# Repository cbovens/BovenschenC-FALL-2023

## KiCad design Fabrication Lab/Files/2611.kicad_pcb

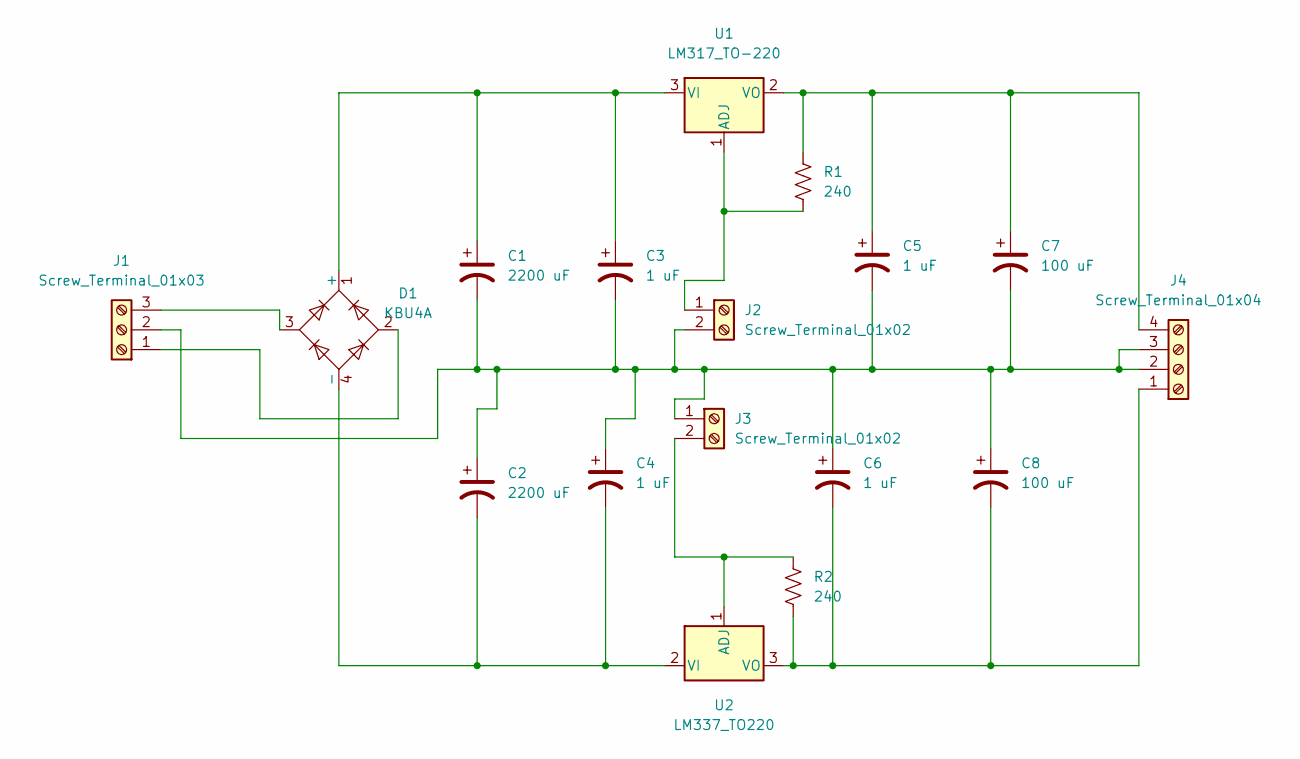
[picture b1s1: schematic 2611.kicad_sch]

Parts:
C1, C2: 2200 uF; CP_Radial_D10.0mm_P5.00mm
C3, C4, C5, C6: 1 uF; CP_Radial_D4.0mm_P2.00mm
C7, C8: 100 uF; CP_Radial_D6.3mm_P2.50mm
D1: KBU4A; Diode_Bridge_Vishay_KBU
J1: Screw_Terminal_01x03; PhoenixContact_MSTBA_2,5_3-G_1x03_P5.00mm_Horizontal
J2, J3: Screw_Terminal_01x02; PhoenixContact_MSTBA_2,5_2-G-5,08_1x02_P5.08mm_Horizontal
J4: Screw_Terminal_01x04; PhoenixContact_MSTBA_2,5_4-G_1x04_P5.00mm_Horizontal
R1, R2: 240; R_Axial_DIN0309_L9.0mm_D3.2mm_P12.70mm_Horizontal
U1: LM317_TO-220; TO-220-3_Vertical
U2: LM337_TO220; TO-220-3_Vertical

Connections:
unnamed: C1.1, C3.1, D1.1 (+), U1.3 (VI)
unnamed: C1.2, C2.1, C3.2, C4.1, C5.2, C6.1, C7.2, C8.1, J1.2, J2.2, J3.1, J4.2, J4.3
unnamed: C2.2, C4.2, D1.4 (-), U2.2 (VI)
unnamed: C6.2, C8.2, J4.1, R2.2, U2.3 (VO)
unnamed: D1.2, J1.1
unnamed: D1.3, J1.3
unnamed: J2.1, R1.2, U1.1 (ADJ)
unnamed: J3.2, R2.1, U2.1 (ADJ)
unnamed: C5.1, C7.1, J4.4, R1.1, U1.2 (VO)

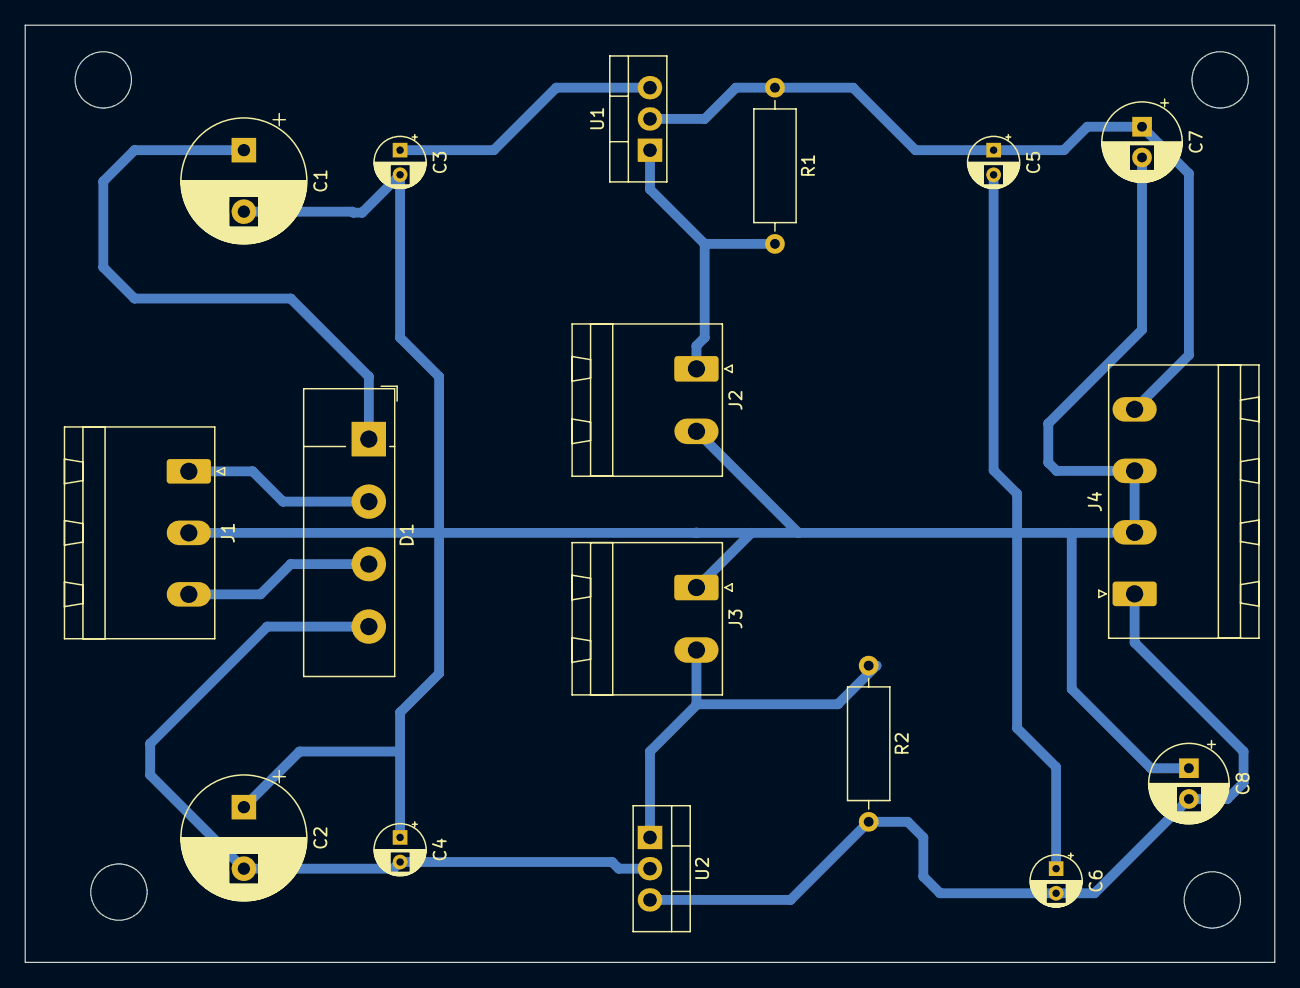
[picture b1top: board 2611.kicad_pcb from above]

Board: 2 copper layers, 101.6 x 76.2 mm, 17 parts (0 on the bottom side), 9 nets.

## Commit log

2023-09-09 NASA-HUNCH-2021
2023-09-12 Video Addition
2023-09-15 PCB Schematics
2023-09-18 DLD Files
